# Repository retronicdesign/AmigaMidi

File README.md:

# Amiga Serial Midi Adapter V1.3

## Schematic

(C)2025 Retronic Design - Open Hardware

## Features
- This serial midi interface is compatible with most Amiga Midi softwares.
- It simply convert serial RS-232 RX and TX signals to MIDI TTL standard.
- MIDI IN is opto-isolated to prevent ground loops and induction noise.
- Self powered via serial port.
- Convenient thru connector to connect other instruments to MIDI IN in daisy-chain.
- Tested on Bar and Pipes professional and OCTA-MED. (Let us know yours!)

## Versions
- v1.0 Initial release
- v1.1 Corrected LED polarity
- v1.2 Corrected DB-25 PCB footprint
- v1.3 Corrected Schematic and PCB (Larger traces / LED alignement / Smaller but capable 5v regulator)

## PCB

## Pictures

*Please note that this picture is an outdated version 1.0 of the serial Midi adapter.

You can have it build at [PCBWay](https://pcbway.com/g/J4X1Dw) under my shared projects.

## Part List

| Quantity | Designator | Part |
| --- | --- | --- |
| 1 |	C1|	100pF |
| 6 |	C2,C3,C4,C5,C6,C7|	0.1uF |
| 1 |	D1 | 1N4148 |
| 2 |	D2,D3 | LED |
| 3 |	J1,J2,J3 | DIN 5 FEMALE |
| 1 |	J4 | D-SUB 25 Female |
| 5 |	R1,R2,R3,R4,R5 | 220 Ohms |
| 2 |	R6,R8 | 1K |
| 1 |	R7 | 3.3K |
| 1 |	U1 | 6N136 |
| 1 |	U2 | MAX232 |
| 1 |	U3 | L4931-5.0 |

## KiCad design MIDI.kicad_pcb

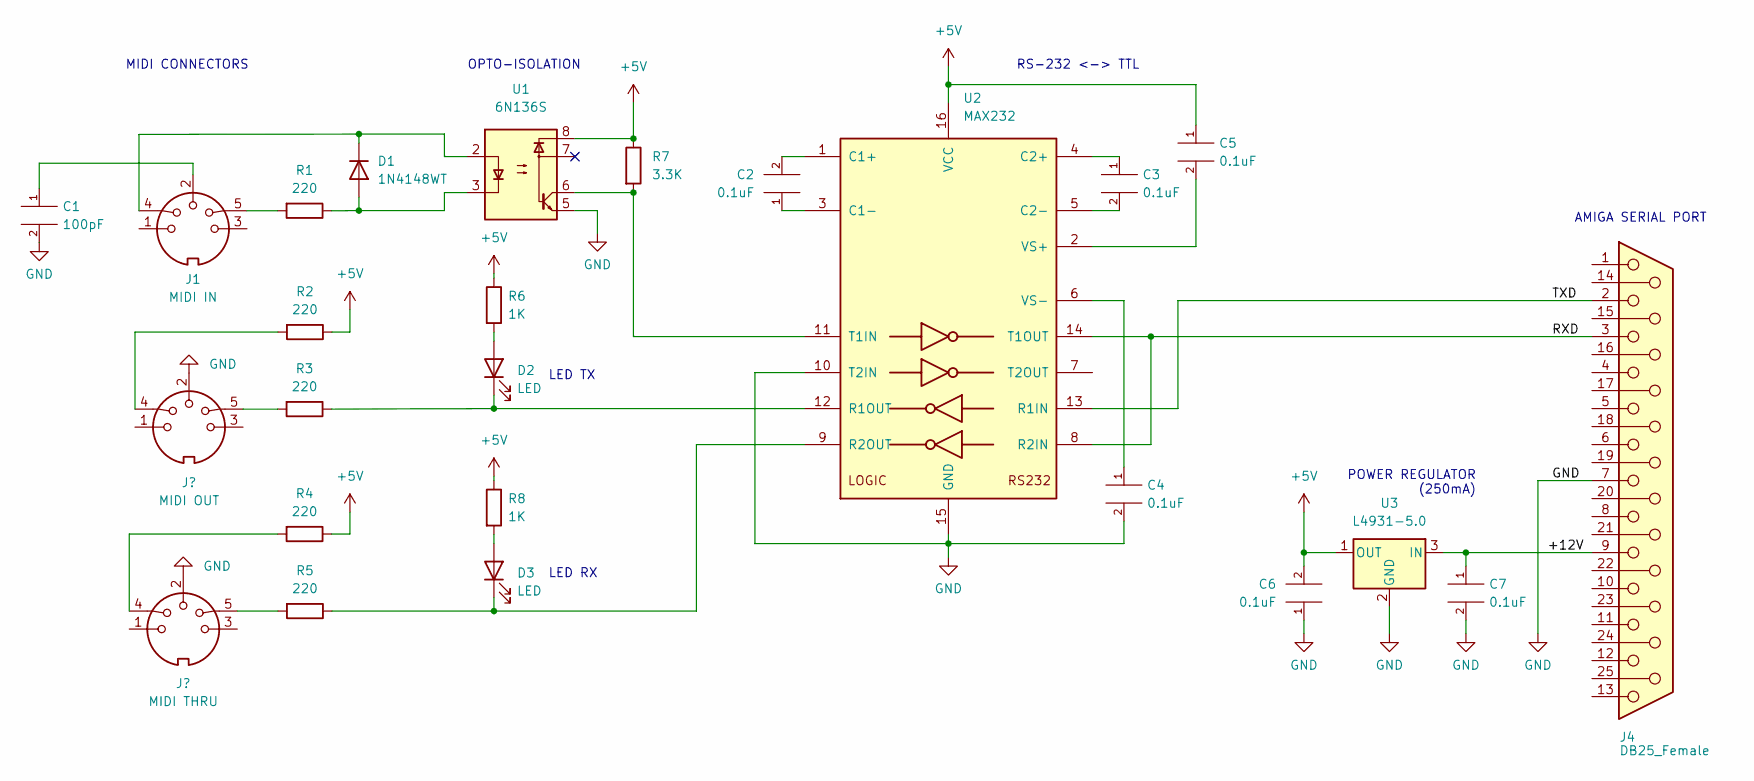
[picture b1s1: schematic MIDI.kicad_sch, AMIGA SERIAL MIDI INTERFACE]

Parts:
C1: 100pF; C_Disc_D3.0mm_W1.6mm_P2.50mm
C2, C3, C4, C5, C6, C7: 0.1uF; C_Disc_D3.0mm_W1.6mm_P2.50mm
D1: 1N4148WT; D_A-405_P7.62mm_Horizontal
D2, D3: LED; LED_D3.0mm
J1: MIDI IN; MIDI_DIN5
J4: DB25_Female; DSUB-25_Female_Horizontal_P2.77x2.84mm_EdgePinOffset7.70mm_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
R1, R2, R3, R4, R5: 220; R_Axial_DIN0204_L3.6mm_D1.6mm_P7.62mm_Horizontal
R6, R8: 1K; R_Axial_DIN0204_L3.6mm_D1.6mm_P7.62mm_Horizontal
R7: 3.3K; R_Axial_DIN0204_L3.6mm_D1.6mm_P7.62mm_Horizontal
U1: 6N136S; DIP-8_W7.62mm_Socket
U2: MAX232; DIP-16_W7.62mm
U3: L4931-5.0; TO-92L_Inline

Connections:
+5V: C5.1, C6.2, R2.1, R4.1, R6.1, R7.1, R8.1, U1.8, U2.16 (VCC), U3.1 (OUT)
/+12V: C7.1, J4.9, U3.3 (IN)
/RXD: J4.3, U2.8 (R2IN), U2.14 (T1OUT)
/TXD: J4.2, U2.13 (R1IN)
GND: C1.2, C4.2, C6.1, C7.2, J4.0, J4.7, U1.5, U2.10 (T2IN), U2.15 (GND), U3.2 (GND); also elsewhere on the board
unnamed: C1.1, J1.2
unnamed: C2.1, U2.3 (C1-)
unnamed: C2.2, U2.1 (C1+)
unnamed: C3.1, U2.4 (C2+)
unnamed: C3.2, U2.5 (C2-)
unnamed: C4.1, U2.6 (VS-)
unnamed: C5.2, U2.2 (VS+)
unnamed: D1.1 (K), J1.4, U1.2
unnamed: D1.2 (A), R1.1, U1.3
unnamed: D2.1 (K), R3.1, U2.12 (R1OUT)
unnamed: D2.2 (A), R6.2
unnamed: D3.1 (K), R5.1, U2.9 (R2OUT)
unnamed: D3.2 (A), R8.2
unnamed: J1.5, R1.2
unnamed 19: R2.2; also elsewhere on the board
unnamed 20: R3.2; also elsewhere on the board
unnamed 21: R4.2; also elsewhere on the board
unnamed 22: R5.2; also elsewhere on the board
unnamed: R7.2, U1.6, U2.11 (T1IN)

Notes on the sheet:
AMIGA SERIAL PORT
MIDI CONNECTORS
LED TX
LED RX
RS-232 <-> TTL
OPTO-ISOLATION
POWER REGULATOR (250mA)

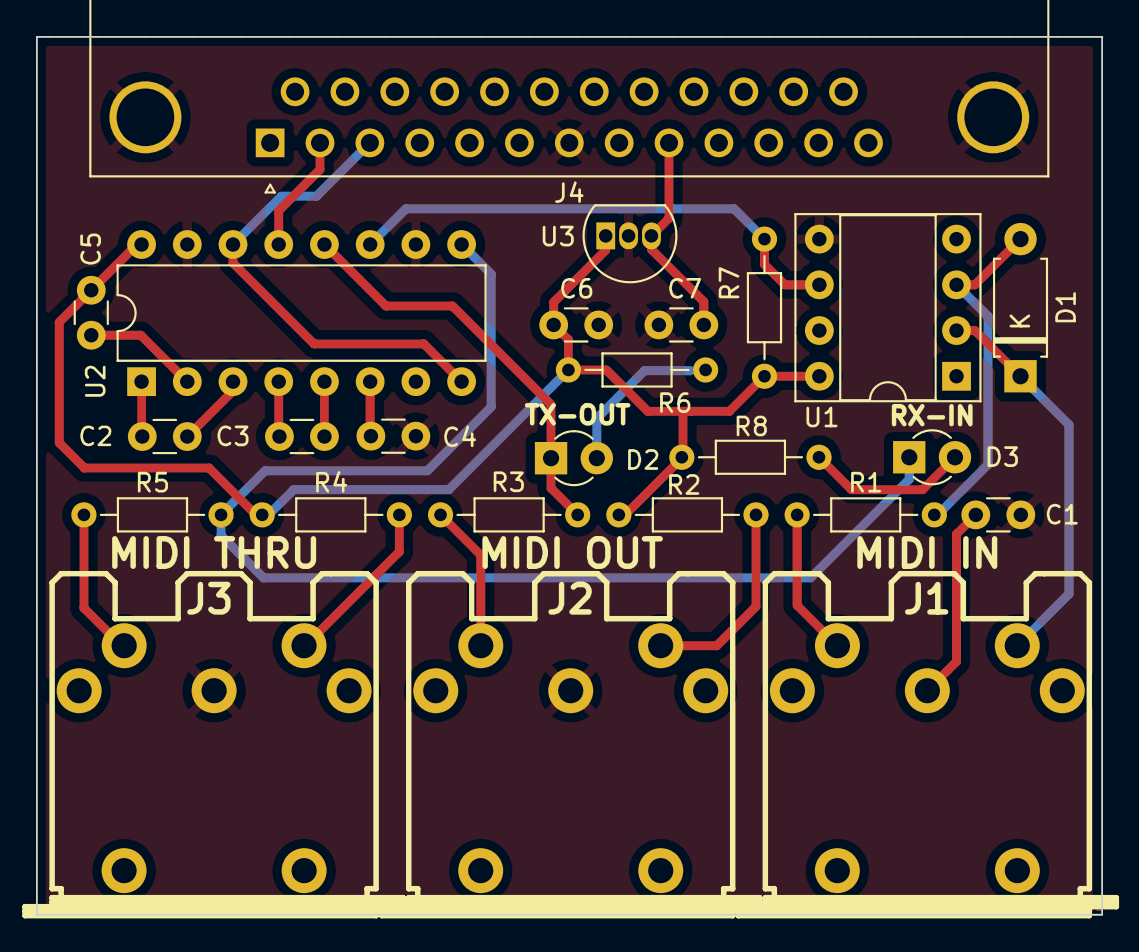
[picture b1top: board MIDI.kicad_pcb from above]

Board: 2 copper layers, 59.2 x 48.8 mm, 25 parts (0 on the bottom side), 24 nets.

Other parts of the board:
J2: MIDI OUT; MIDI_DIN5
J3: MIDI THRU; MIDI_DIN5

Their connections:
GND: J2.2, J3.2; also elsewhere on the board
unnamed 19: J2.4; also elsewhere on the board
unnamed 20: J2.5; also elsewhere on the board
unnamed 21: J3.4; also elsewhere on the board
unnamed 22: J3.5; also elsewhere on the board
